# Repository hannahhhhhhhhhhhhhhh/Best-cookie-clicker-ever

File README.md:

# Best-cookie-clicker-ever: cookie Clicker with a Gambling Mode

This is a small handheld game pad built around the Seeed XIAO RP2040 and a 1.8" 128x160 TFT screen. It runs a cookie clicker game, tap keys to earn clicks, unlock a bonus key at 5,000 clicks, and gamble your clicks on a 50/50 double or nothing roll, good luck :3 It is a custom PCB designed in KiCad

And I wrote hackclub all over it because hackclub is goated 

## Why I Made This
There are online cookie clickers. But I think I real one needs actual mechanical keys that look pretty and its own screen. So with a display, the first thing that came to my mind is I want to make a keypad that displays the amount of clicks. 
Also who doesn't like gambling
I am making this for my friend who likes geometry dash so he probably likes clicking keys.

## How It Works

### Controls

| Key | Normal mode | Gamble mode |
|-----|-------------|-------------|
| SW1 (top left) | +1 click | +1 click |
| SW4 (top right) | Locked until you reach 5,000 clicks, then +2 clicks per press | Same |
| SW5 (middle left) | Enter gamble mode | Leave gamble mode |
| SW2 (middle right) | Nothing | Confirm the bet and roll |
| SW6 (bottom left) | Nothing | Bet +100 (hold to repeat) |
| SW3 (bottom right) | Nothing | Bet -100 (hold to repeat) |

Hold SW6 and SW3 together for 3 seconds to wipe the saved game.

### Game features

- **Click counter:** the screen shows your total clicks with thousands separators. Theres a progress bar fills toward the 5,000 click unlock.
- **Gambling:** the bet starts at 100 and moves in steps of 100, capped by how many clicks you have. A roll is a true 50/50 using the RP2040's hardware random number generator. A win doubles your bet, a loss loses it.
- **Fair saves:** the bet is taken out and saved to flash before the roll happens muahahahaha
- **Progress:** clicks, wins, losses and the bonus unlock are saved to flash and restored on power up.
- Random ASCII art (a cookie, a cat, a rocket, a star etc) pops up at random positions while you click. Gamble mode has its own dice, win and skull art.
  
### The circuit

- **Microcontroller:** Seeed XIAO RP2040 (U1).
- **Keys:** each of the 6 switches connects one GPIO pin to GND. The firmware turns on the RP2040's internal pull-up resistors, so a pressed key reads LOW and no external resistors are needed. The firmware debounces each key for 15 ms.
- **Screen:** the 1.8" ST7735 TFT module connects through the 8-pin header J1 and talks over hardware SPI0 (SCK on GPIO2, MOSI on GPIO3). The screen is write only, so MISO is not used. That frees GPIO4, which is why the +100 key is on that pin, and the firmware explicitly releases it from SPI.
- **Power:** everything runs from USB-C through the XIAO. The screen is powered from the XIAO's 3.3V pin.

| Signal | XIAO pin | GPIO |
|--------|----------|------|
| TFT SCK | D8 | GPIO2 |
| TFT MOSI | D10 | GPIO3 |
| TFT CS | D7 | GPIO1 |
| TFT DC | D6 | GPIO0 |
| TFT RST | D3 | GPIO29 |
| SW1 (click) | D0 | GPIO26 |
| SW2 (confirm) | D1 | GPIO27 |
| SW3 (bet -100) | D2 | GPIO28 |
| SW4 (gold key) | D4 | GPIO6 |
| SW5 (gamble) | D5 | GPIO7 |
| SW6 (bet +100) | D9 | GPIO4 |

### The PCB

The board is a single PCB with the XIAO and screen header on the left, six hot swap key switches in a 2 by 3 grid on the right, and custom silkscreen art. I made this board small so it is more portable and I chose keys that is assembled directly on the pcb. 

## Bill of Materials

| Item | Qty | Supplier | Cost/Item (CAD) | Total Cost (CAD) | Link |
|------|-----|----------|-----------------|------------------|------|
| Seeed XIAO RP2040 | 1 | Seed studio | $4.9 | $4.9 | [[link]](seeedstudio.com/Seeed-Studio-XIAO-RP2040-Plus-p-6932.html?c_event_medium=search%3A%3Aresults&c_event_id=4057244488%3A%3ASeeed+XIAO+RP2040) |
| 1.8" 128x160 ST7735 TFT module (SPI, 8 pin) | 1 | Canada Robotics | $12.99 | $12.99 | [[link]](https://www.canadarobotix.com/products/3056?srsltid=AYCX9vLb8w1gLBkC4ExwkK73b0u5_ToArs0HsUIRm7UbcOfMoLzOpVDB) |
| Key switches | 6 | YUNZII | $12.99 | $12.99 | [[link]](https://www.canadacomputers.com/en/keyboard-switches/285141/yunzii-milk-v2-linear-switch-35-pieces-per-pack-milk-v2.html) |
| Keycaps | 6 | Canada computers | $24.99 | $24.99 | [[link]](https://www.canadacomputers.com/en/keycaps/281092/keychron-artisan-keycap-galaxy-resin-sa-keycaps-rt-32.html) |
| PCB fabrication (JLCPCB) | 1 | JLCPCB | $14.99 | $14.99 | [[link]](https://jlcpcb.com/) |
| | | | **Total** | **$70.86** | |

## Firmware Flashing Guide

The firmware is a single Arduino sketch:
### What you need

- Arduino IDE 2.x 
- A USB-C data cable
- The assembled pcb with the XIAO RP2040 and TFT module attached

### 1. Install the RP2040 board package

1. Open Arduino IDE and go to **File > Preferences**.
2. Go to **Tools > Board > Boards Manager**, search for `pico`, and install **Raspberry Pi Pico/RP2040** by Earle F. Philhower, III.

### 2. Install the libraries

Go to **Sketch > Include Library > Manage Libraries** and install:

- **Adafruit GFX Library**
- **Adafruit ST7735 and ST7789 Library**
install the dependencies

### 3. Open the sketch

Get the ino file in this repo, the sketch must stay inside a folder named `cookie_clicker`, or Arduino IDE will ask to move it.

### 4. Select the board

Go to **Tools > Board > Raspberry Pi Pico/RP2040 > Seeed XIAO RP2040**.

### 5. Put the XIAO in bootloader mode and upload

1. Hold the B button on the XIAO and plug it into your computer over USB-C. Release the button. A drive named `RPI-RP2` appears.
2. In Arduino IDE, select the new port under **Tools > Port**. If no port shows yet, you can still press Upload and the IDE will find the board.
3. Click the **Upload** button (right arrow, top left).
4. Wait for the upload to finish. The board reboots by itself and the game starts on the screen.

After the first upload, you can upload again without the boot button.

### Troubleshooting
If! you want to reset your save: hold SW6 and SW3 together for 3 seconds.

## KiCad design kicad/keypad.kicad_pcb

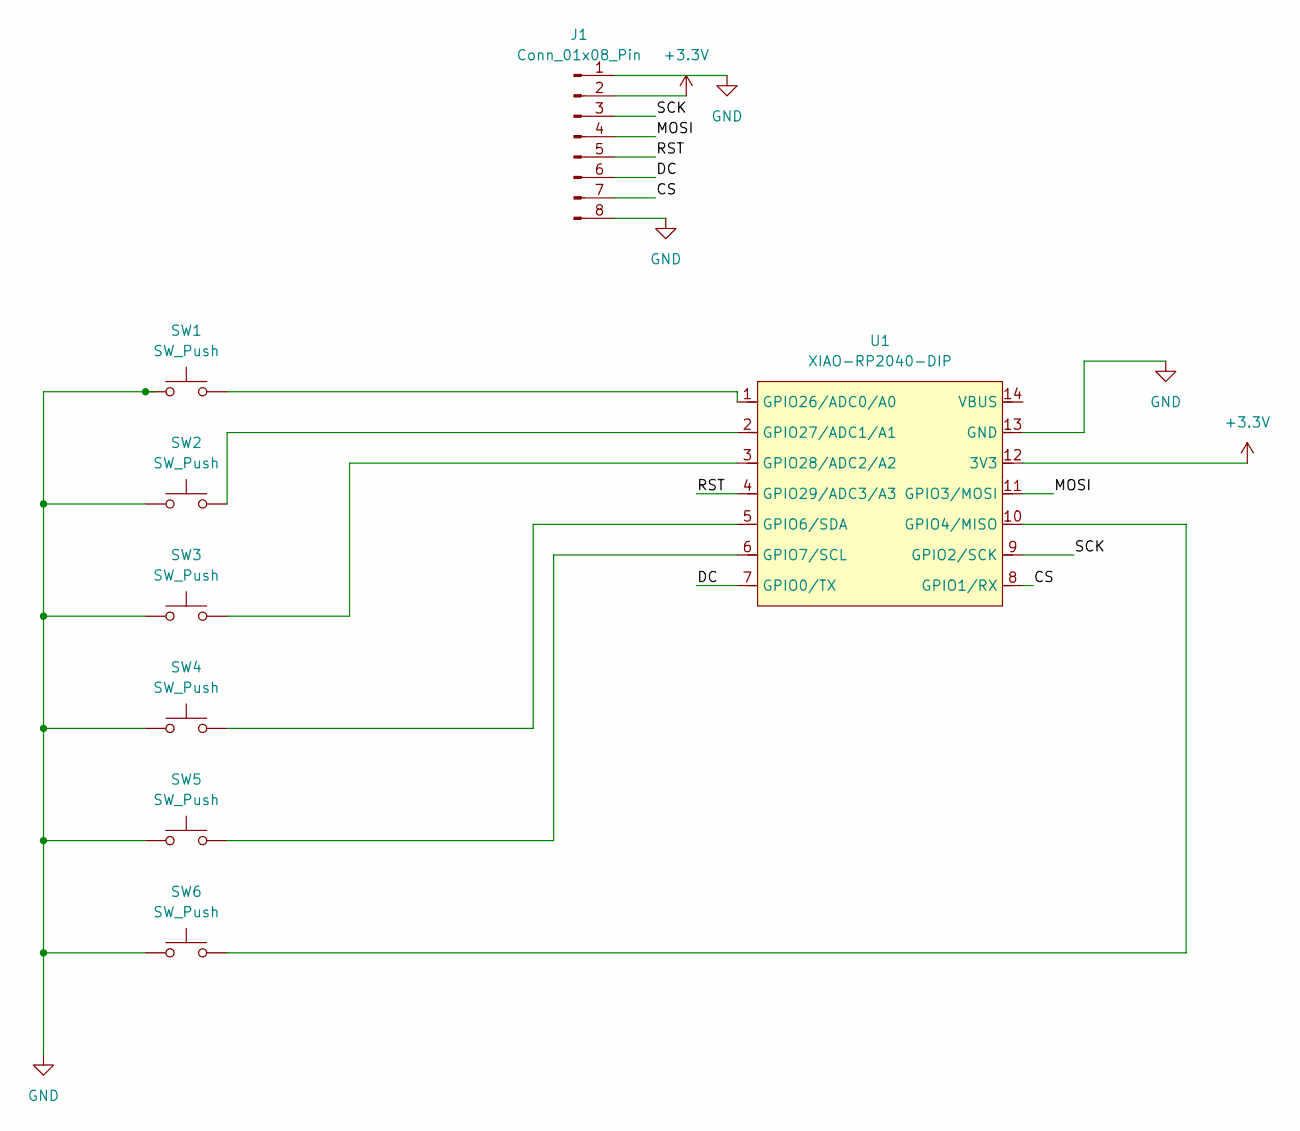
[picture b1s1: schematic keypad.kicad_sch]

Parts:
J1: Conn_01x08_Pin; PinHeader_1x08_P2.54mm_Vertical
SW1, SW2, SW3, SW4, SW5, SW6: SW_Push; SW_Cherry_MX_1.00u_PCB
U1: XIAO-RP2040-DIP

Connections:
+3.3V: J1.2, U1.12 (3V3)
/CS: J1.7, U1.8 (GPIO1/RX)
/DC: J1.6, U1.7 (GPIO0/TX)
/MOSI: J1.4, U1.11 (GPIO3/MOSI)
/RST: J1.5, U1.4 (GPIO29/ADC3/A3)
/SCK: J1.3, U1.9 (GPIO2/SCK)
GND: J1.1, J1.8, SW1.1, SW2.1, SW3.1, SW4.1, SW5.1, SW6.1, U1.13 (GND)
unnamed: SW6.2, U1.10 (GPIO4/MISO)
unnamed: SW4.2, U1.5 (GPIO6/SDA)
unnamed: SW5.2, U1.6 (GPIO7/SCL)
unnamed: SW1.2, U1.1 (GPIO26/ADC0/A0)
unnamed: SW2.2, U1.2 (GPIO27/ADC1/A1)
unnamed: SW3.2, U1.3 (GPIO28/ADC2/A2)

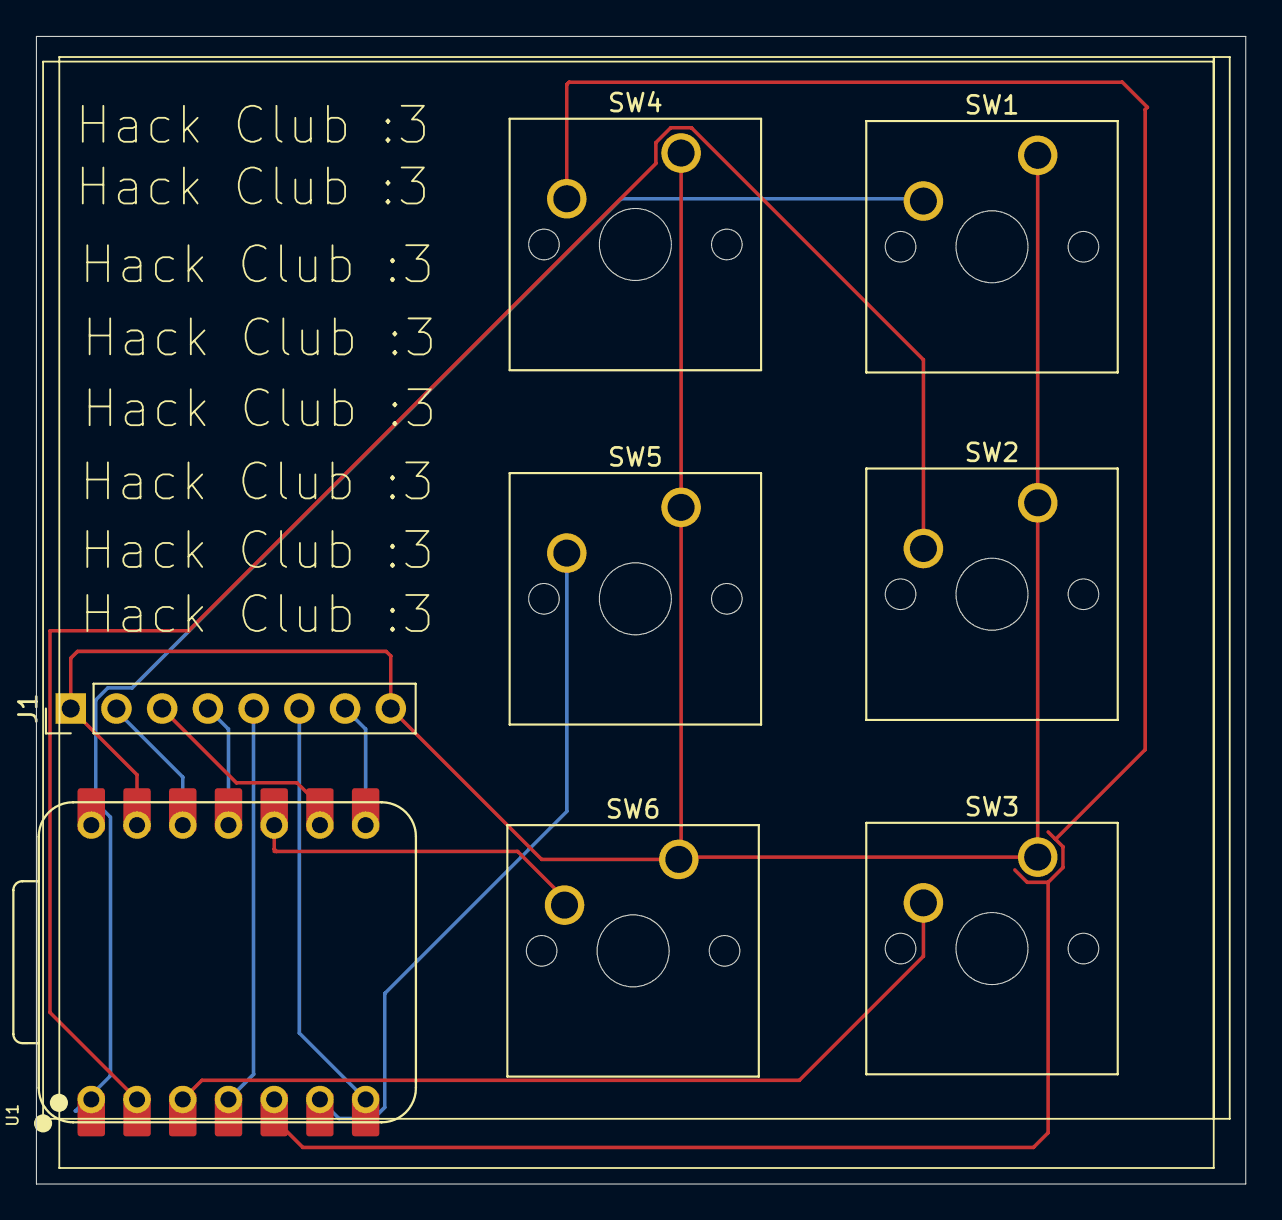
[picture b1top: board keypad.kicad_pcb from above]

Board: 2 copper layers, 67.2 x 63.8 mm, 8 parts (0 on the bottom side), 13 nets.
